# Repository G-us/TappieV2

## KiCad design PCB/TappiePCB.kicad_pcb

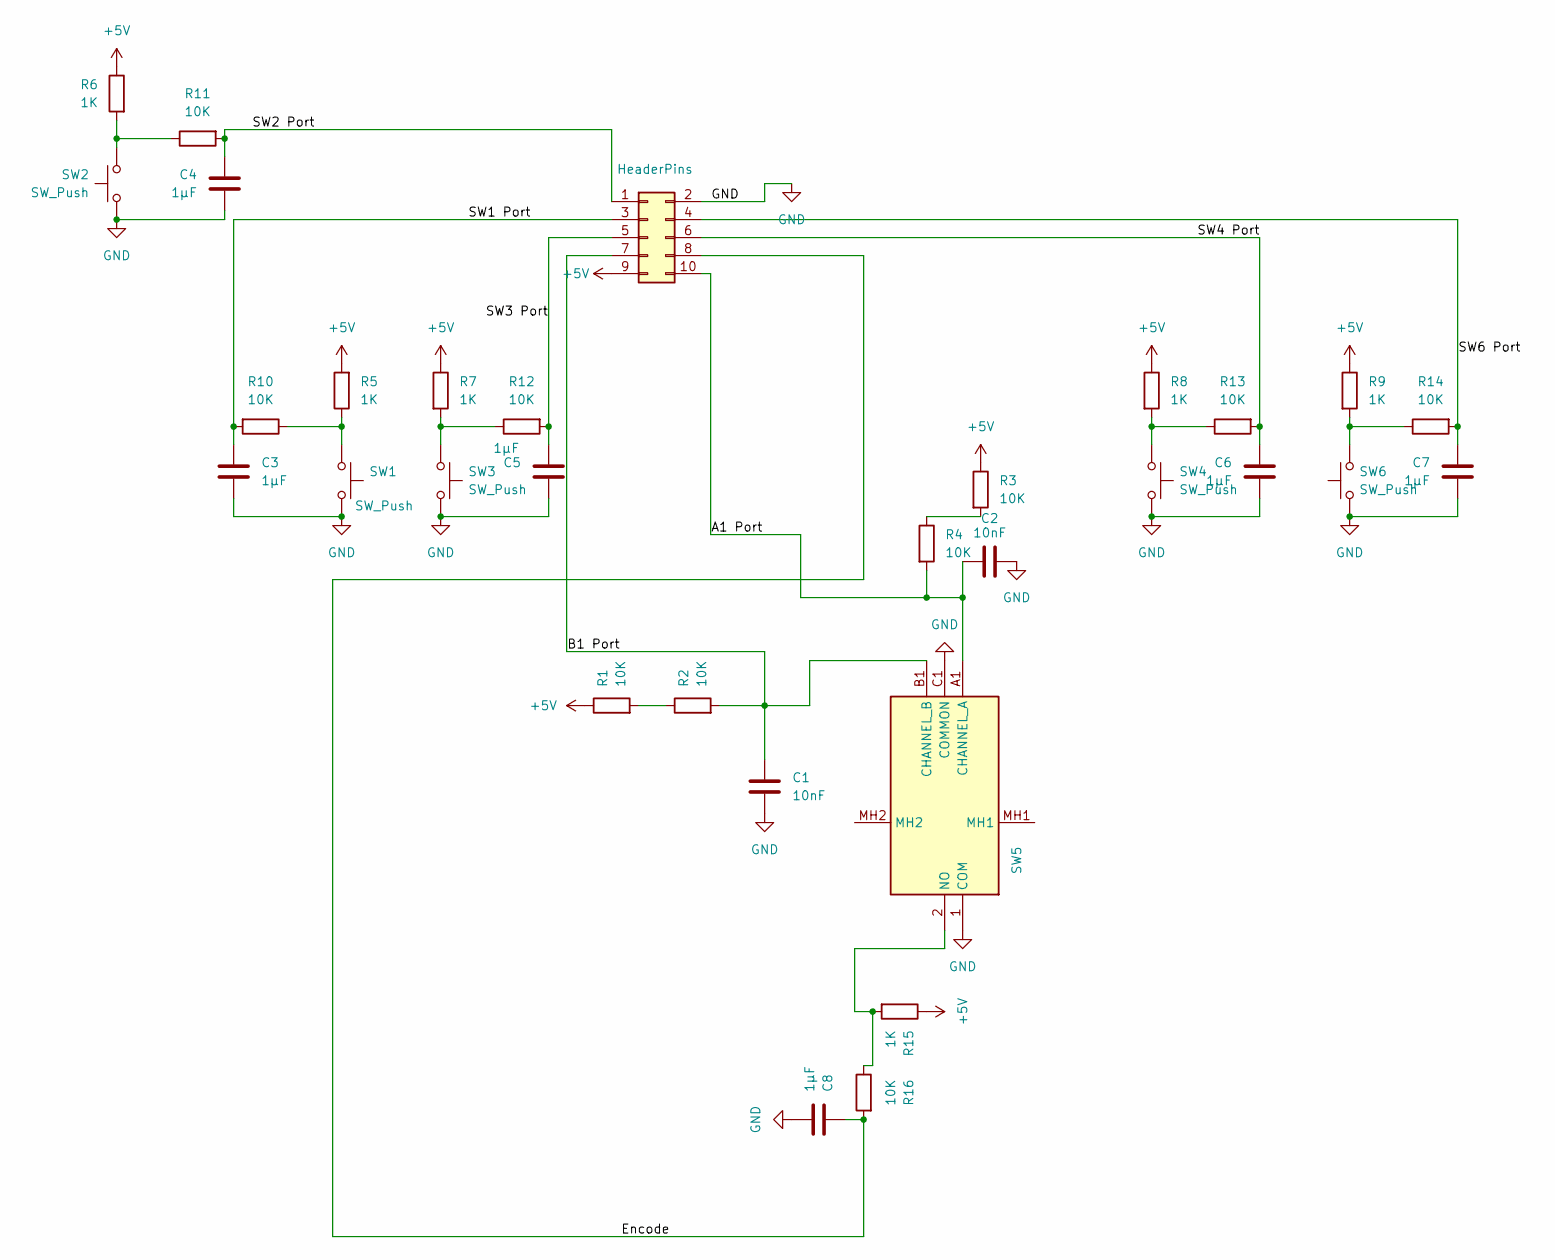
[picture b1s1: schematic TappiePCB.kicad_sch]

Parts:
C1, C2: 10nF; C_0805_2012Metric_Pad1.18x1.45mm_HandSolder
C3, C4, C5, C6, C7, C8: 1μF; C_0805_2012Metric_Pad1.18x1.45mm_HandSolder
J1: HeaderPins; PinHeader_2x05_P2.54mm_Vertical
R1, R2, R3, R4, R10, R11, R12, R13, R14, R16: 10K; R_0805_2012Metric_Pad1.20x1.40mm_HandSolder
R5, R6, R7, R8, R9, R15: 1K; R_0805_2012Metric_Pad1.20x1.40mm_HandSolder
SW1, SW2, SW3, SW4, SW6: SW_Push; SW_PUSH-12mm3D
SW5: RotaryEncoder_Switch_MP; PEC11R4215FS0024; Mouser Part Number 652-PEC11R-4215F-S24

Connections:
+5V: J1.9, R1.1, R3.1, R5.2, R6.1, R7.1, R8.1, R9.1, R15.1
/A1 Port: C2.1, J1.10, R4.2, SW5.A1 (CHANNEL_A)
/B1 Port: C1.2, J1.7, R2.2, SW5.B1 (CHANNEL_B)
/Encode: C8.1, J1.8, R16.2
/SW1 Port: C3.1, J1.3, R10.2
/SW2 Port: C4.1, J1.1, R11.2
/SW3 Port: C5.1, J1.5, R12.2
/SW4 Port: C6.1, J1.6, R13.2
/SW6 Port: C7.1, J1.4, R14.2
GND: C1.1, C2.2, C3.2, C4.2, C5.2, C6.2, C7.2, C8.2, J1.2, SW1.2, SW2.2, SW3.2, SW4.2, SW5.1 (COM), SW5.C1 (COMMON), SW6.1
unnamed: R1.2, R2.1
unnamed: R3.2, R4.1
unnamed: R5.1, R10.1, SW1.1
unnamed: R6.2, R11.1, SW2.1
unnamed: R7.2, R12.1, SW3.1
unnamed: R8.2, R13.1, SW4.1
unnamed: R9.2, R14.1, SW6.2
unnamed: R15.2, R16.1, SW5.2 (NO)

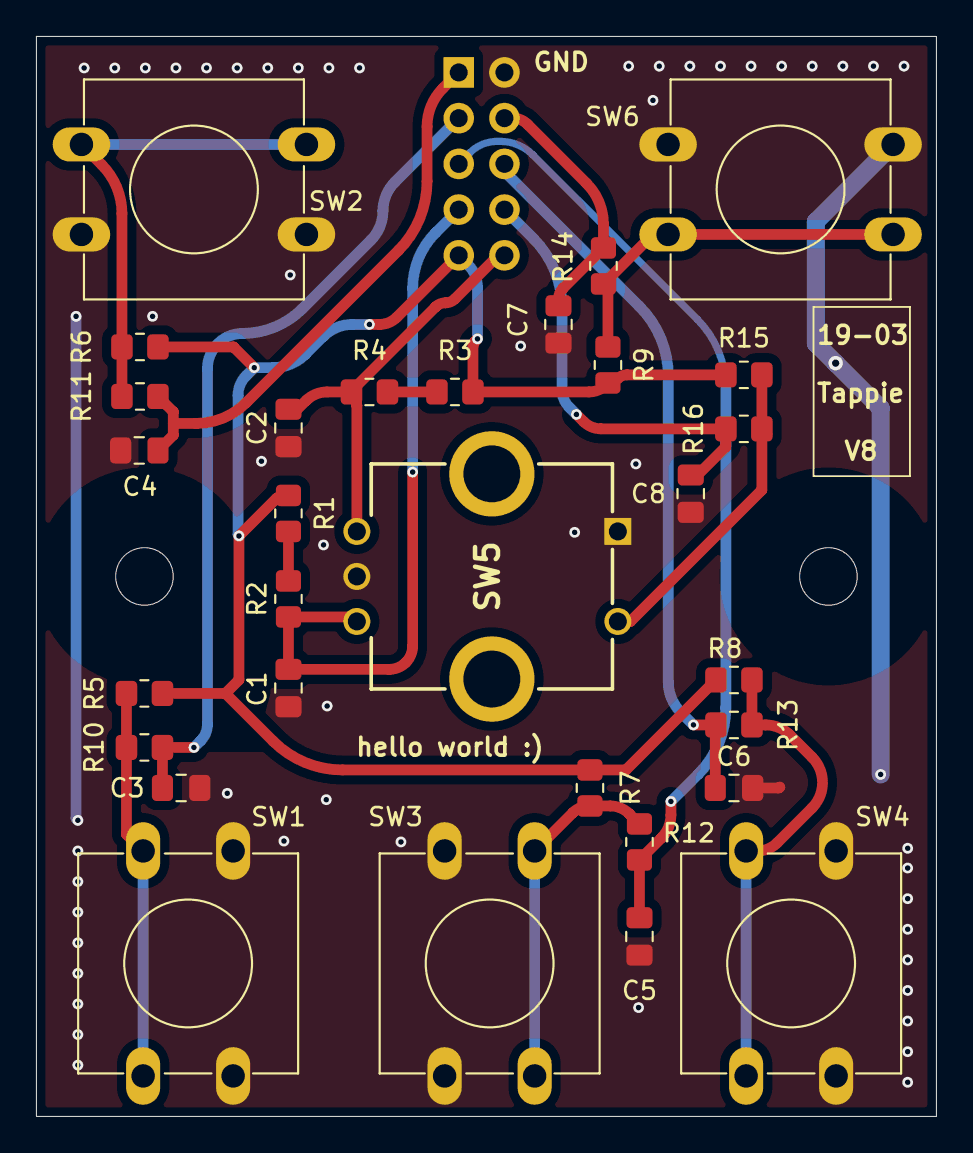
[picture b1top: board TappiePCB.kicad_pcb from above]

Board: 2 copper layers, 50.0 x 60.0 mm, 31 parts (1 on the bottom side), 18 nets.

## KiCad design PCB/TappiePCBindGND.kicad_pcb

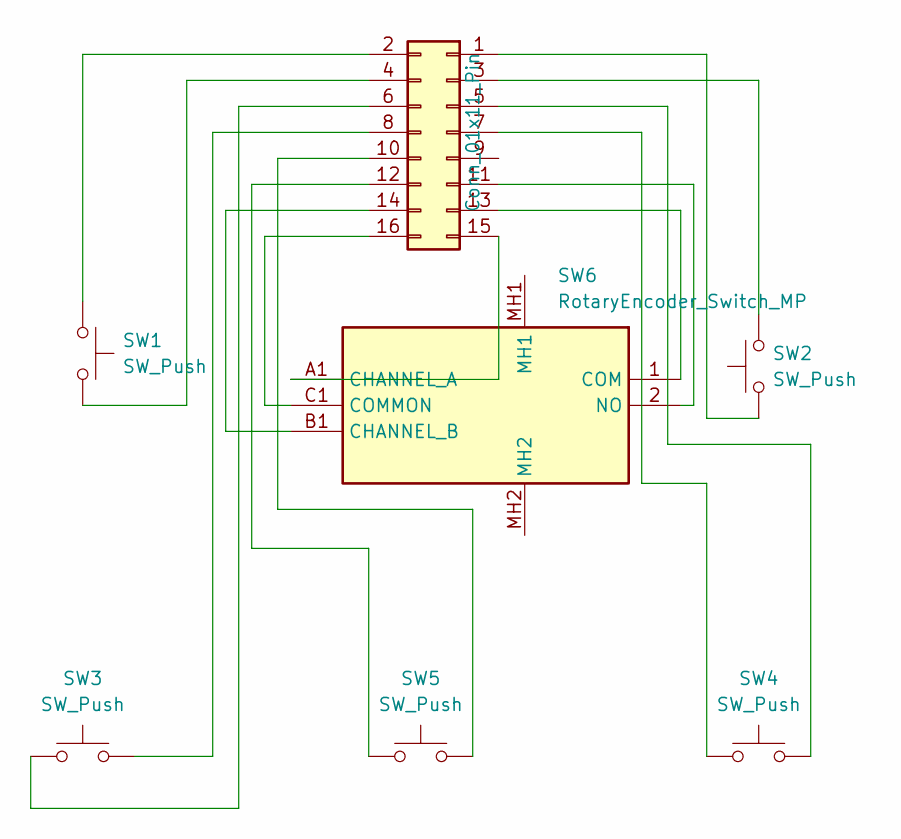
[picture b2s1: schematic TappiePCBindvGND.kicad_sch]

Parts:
J1: Conn_01x11_Pin; PinHeader_2x08_P2.54mm_Vertical
SW1, SW2, SW3, SW4, SW5: SW_Push; SW_PUSH-12mm3D
SW6: RotaryEncoder_Switch_MP; PEC11R4215FS0024; Mouser Part Number 652-PEC11R-4215F-S24

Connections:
unnamed: J1.1, SW2.1
unnamed: J1.2, SW1.1
unnamed: J1.3, SW2.2
unnamed: J1.4, SW1.2
unnamed: J1.5, SW4.2
unnamed: J1.6, SW3.1
unnamed: J1.7, SW4.1
unnamed: J1.8, SW3.2
unnamed: J1.10, SW5.2
unnamed: J1.11, SW6.2 (NO)
unnamed: J1.12, SW5.1
unnamed: J1.13, SW6.1 (COM)
unnamed: J1.14, SW6.B1 (CHANNEL_B)
unnamed: J1.15, SW6.A1 (CHANNEL_A)
unnamed: J1.16, SW6.C1 (COMMON)

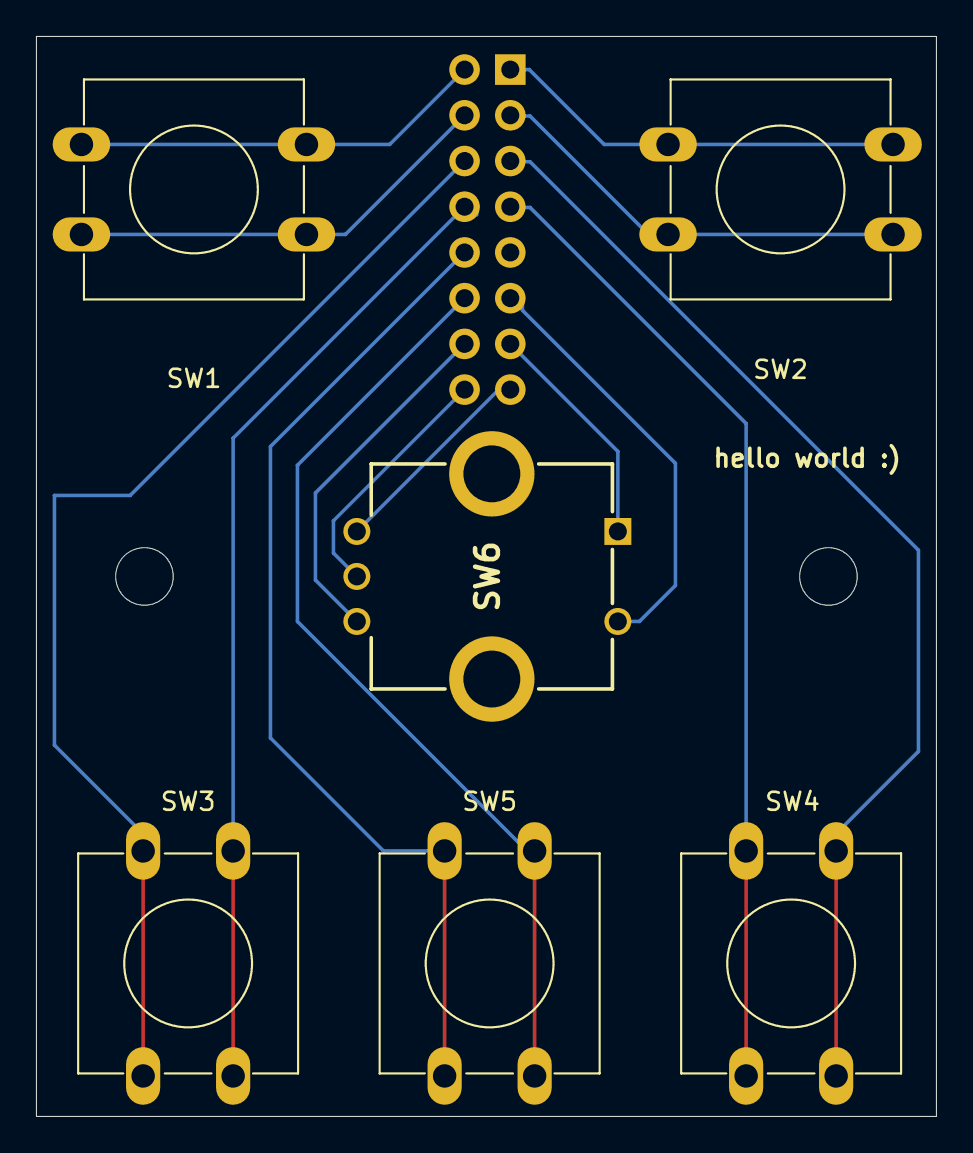
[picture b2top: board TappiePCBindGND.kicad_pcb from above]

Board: 2 copper layers, 50.0 x 60.0 mm, 7 parts (1 on the bottom side), 15 nets.

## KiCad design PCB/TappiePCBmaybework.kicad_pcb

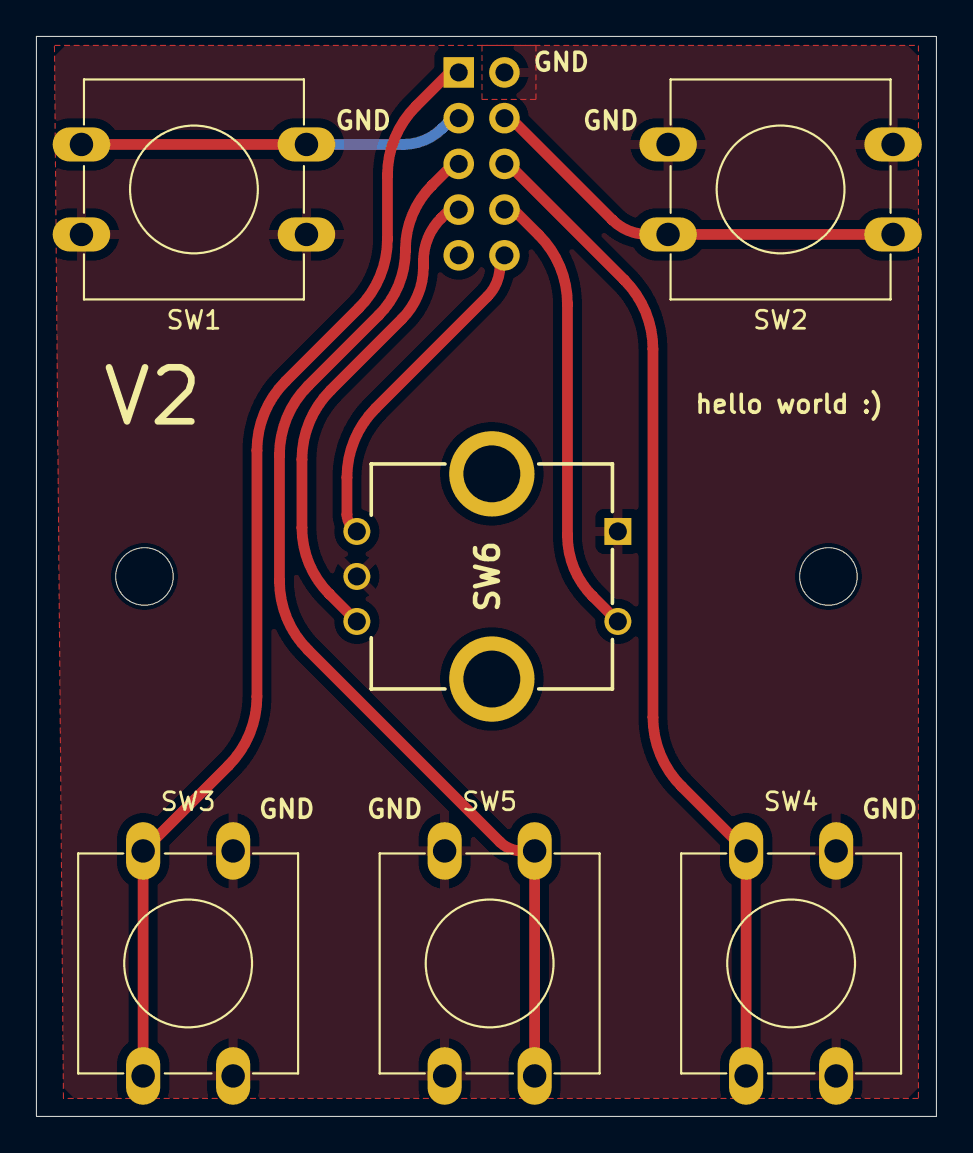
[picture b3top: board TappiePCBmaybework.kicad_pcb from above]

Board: 2 copper layers, 50.0 x 60.0 mm, 7 parts (1 on the bottom side), 9 nets.

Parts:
J1: HeaderPins; PinHeader_2x05_P2.54mm_Vertical
SW1, SW2, SW3, SW4, SW5: SW_Push; SW_PUSH-12mm3D
SW6: RotaryEncoder_Switch_MP; PEC11R4215FS0024

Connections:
unnamed: J1.1, SW3.1
unnamed: J1.2, SW1.2, SW2.1, SW3.2, SW4.2, SW5.2, SW6.1 (COM), SW6.C1 (COMMON)
unnamed: J1.3, SW1.1
unnamed: J1.4, SW2.2
unnamed: J1.5, SW5.1
unnamed: J1.6, SW4.1
unnamed: J1.7, SW6.B1 (CHANNEL_B)
unnamed: J1.8, SW6.2 (NO)
unnamed: J1.10, SW6.A1 (CHANNEL_A)

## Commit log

2025-03-19 Added KiCad Files
2025-03-20 Added ESP32 code, reorganized
2025-03-20 added gitignore
2025-03-20 added python file
2025-04-14 Update .gitignore and refactor main.cpp for BLE integration
2025-04-14 Add BLE characteristic and simplify device connection logic
2025-04-24 Refactor main.py to simplify device discovery and remove unused logging and connection code; add new PCB configuration files.
2025-04-24 Add Tappie V2 BLE Client Application with audio control features
    - Introduced new audio control application for Tappie device using BLE.
    - Implemented volume adjustment based on rotary encoder input.
    - Added support for media button actions (single, double, multi-click).
    - Integrated audio feedback with sound files for button actions and connection events.
    - Created a TODO file for future enhancements including battery reporting and taskbar icon.
    - Added old ESP32 code and previous main application for reference.
2025-04-25 Refactor main.py to improve battery level handling and add notifications; update TODO list and add new media files
2025-04-25 Implement deep sleep mode and reed switch handling; refactor media button setup and notification logic
2025-04-25 Refactor main.cpp to include WiFi library and disable WiFi during setup; update TappieV2PC.py to improve battery level handling and tooltip updates.
2025-04-26 Enhance power management features by adding light sleep mode, optimizing GPIO configurations, and disabling unused peripherals; update CPU frequency handling and improve BLE connection parameters for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
2025-04-26 Refactor main.cpp to optimize GPIO configurations and update reed switch pin; add audio device icons in TappieV2PC.py and improve tooltip handling; include new icon files for enhanced UI feedback.
2025-04-26 screw this AI. i updated the battery showing so it should say N/A less often
2025-04-26 made it so that the battery auto reports every 5 min,this way the battery level should always be more accurate
2025-04-26 added little silly noises with volume and fixed device selection notification
2025-04-27 updated icons tihi
2025-05-02 small little thing to prevent battery level from always giving notificiations
2025-05-03 added some little battery shenanigans
2025-05-03 refactored folders
2025-05-03 remove old files and implement new Tappie V2 controller with battery handling
2025-05-03 changed default battery level
2025-05-07 to tired for this shit. did things. mo money mo problems. i hate the esp32-c3
2025-05-09 ummm yeahh
2025-05-10 fix: update encoder switch pin and improve battery level reading
2025-05-11 added lib
2025-05-12 gave library another go, not so bad
2025-05-12 fix: improve encoder position handling and add error management for BLE services
2025-05-16 Refactor GPIO pin assignments and remove unused files
    - Changed ChatButtonPin from 9 to 5 to avoid pin conflict with reed switch.
    - Deleted main.txt and mainv2.txt files as they were redundant and not in use.
    - Removed nobutlikefrusethisoneasofthursdaynight.txt to clean up the project structure.
